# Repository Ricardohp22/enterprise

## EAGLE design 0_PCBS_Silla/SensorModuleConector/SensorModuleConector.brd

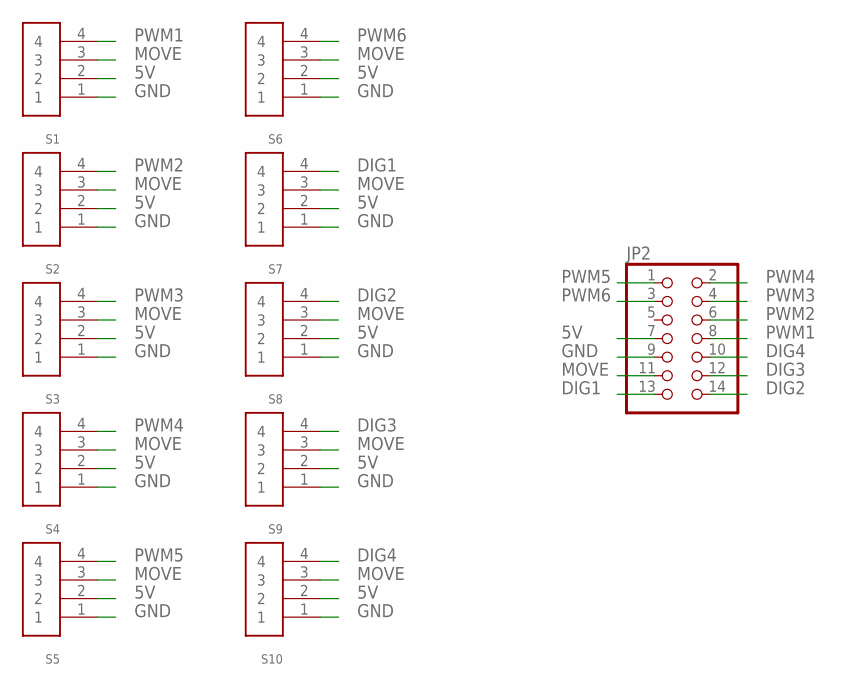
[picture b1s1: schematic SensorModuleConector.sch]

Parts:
JP2: PINHD-2X7; 2X07
S1, S2, S3, S4, S5, S6, S7, S8, S9, S10: CP150_1X4

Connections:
5V: JP2.7, S1.2, S2.2, S3.2, S4.2, S5.2, S6.2, S7.2, S8.2, S9.2, S10.2
DIG1: JP2.13, S7.4
DIG2: JP2.14, S8.4
DIG3: JP2.12, S9.4
DIG4: JP2.10, S10.4
GND: JP2.9, S1.1, S2.1, S3.1, S4.1, S5.1, S6.1, S7.1, S8.1, S9.1, S10.1
MOVE: JP2.11, S1.3, S2.3, S3.3, S4.3, S5.3, S6.3, S7.3, S8.3, S9.3, S10.3
PWM1: JP2.8, S1.4
PWM2: JP2.6, S2.4
PWM3: JP2.4, S3.4
PWM4: JP2.2, S4.4
PWM5: JP2.1, S5.4
PWM6: JP2.3, S6.4

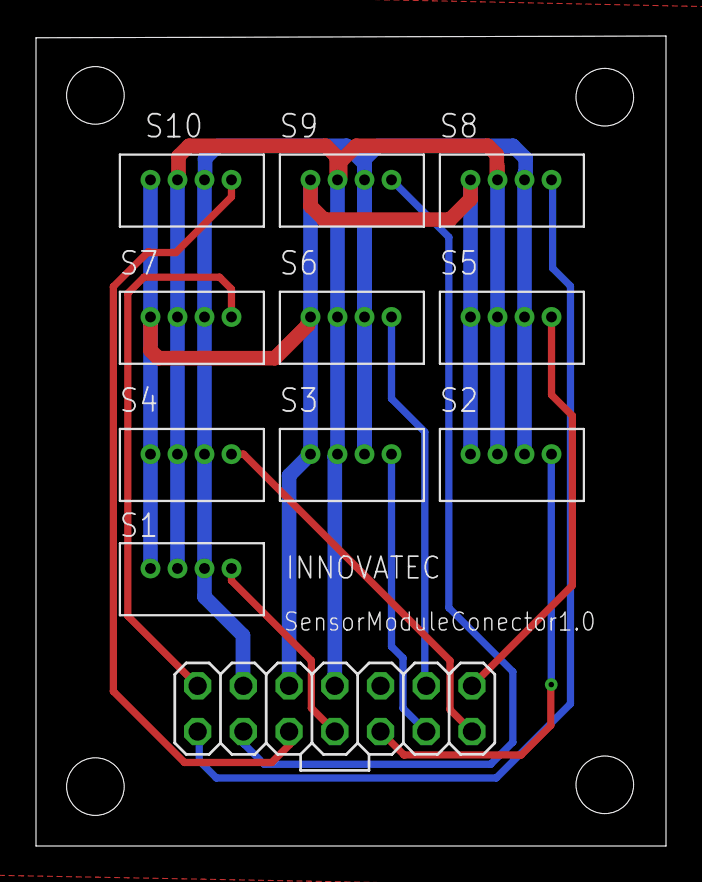
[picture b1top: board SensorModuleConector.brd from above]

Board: 2 copper layers, 35.0 x 45.0 mm, 11 parts (0 on the bottom side), 13 nets.

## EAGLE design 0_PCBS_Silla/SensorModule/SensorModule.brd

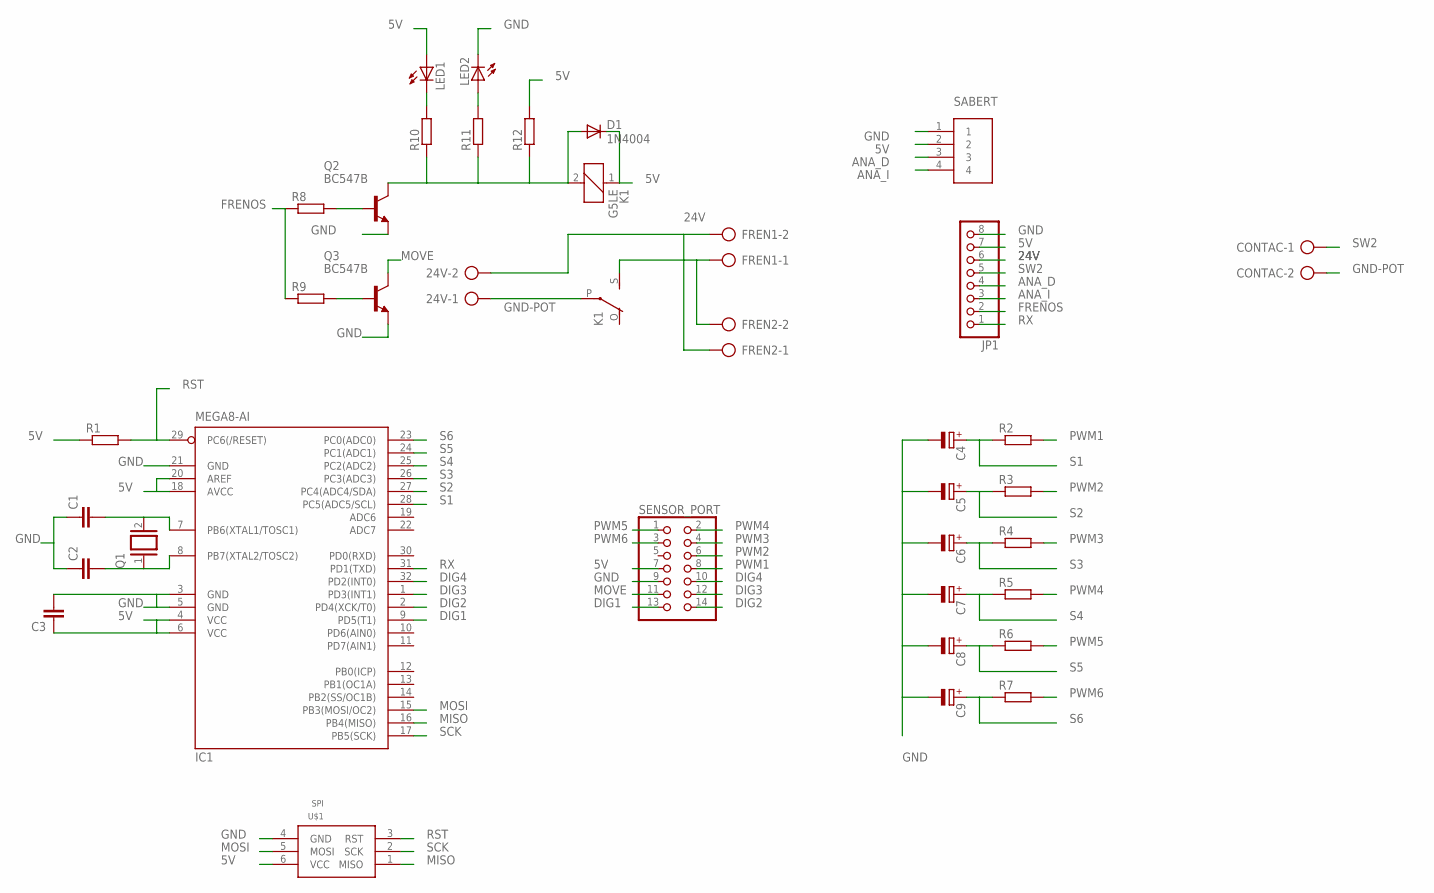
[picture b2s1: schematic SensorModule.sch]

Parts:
24V: AK500/2
C1, C2, C3: C-EUC0402K; C0402K
C4, C5, C6, C7, C8, C9: CPOL-EU153CLV-0505; 153CLV-0505
CONTAC: AK500/2
D1: 1N4004; DO41-10
FREN1, FREN2: AK500/2
IC1: MEGA8-AI; TQFP32-08
JP1: PINHD-1X8; 1X08
K1: G5LE
LED1, LED2: LEDCHIP-LED0603; CHIP-LED0603
Q1: XTAL/S; QS
Q2, Q3: BC547B; TO92
R1, R2, R3, R4, R5, R6, R7, R8, R9, R10, R11, R12: R-EU_M1206; M1206
SABERT: CP2_1X4
SENSOR_PORT: PINHD-2X7; 2X07
U$1: SPI; HEAD-2X3

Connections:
5V: C3.1, D1.C, IC1.4 (VCC), IC1.6 (VCC), IC1.18 (AVCC), IC1.20 (AREF), JP1.7, K1.1, LED1.A, R1.1, R12.2, SABERT.2, SENSOR_PORT.7, U$1.6 (VCC)
24V: 24V.2, FREN1.2, FREN2.1, JP1.6
ANA_D: JP1.4, SABERT.3
ANA_I: JP1.3, SABERT.4
DIG1: IC1.9 (PD5(T1)), SENSOR_PORT.13
DIG2: IC1.2 (PD4(XCK/T0)), SENSOR_PORT.14
DIG3: IC1.1 (PD3(INT1)), SENSOR_PORT.12
DIG4: IC1.32 (PD2(INT0)), SENSOR_PORT.10
FRENOS: JP1.2, R8.1, R9.1
GND: C1.1, C2.1, C3.2, C4.-, C5.-, C6.-, C7.-, C8.-, C9.-, IC1.3 (GND), IC1.5 (GND), IC1.21 (GND), JP1.8, LED2.C, Q2.1 (E), Q3.1 (E), SABERT.1, SENSOR_PORT.9, U$1.4 (GND)
GND-POT: 24V.1, CONTAC.2, K1.P
MISO: IC1.16 (PB4(MISO)), U$1.1 (MISO)
MOSI: IC1.15 (PB3(MOSI/OC2)), U$1.5 (MOSI)
MOVE: Q3.3 (C), SENSOR_PORT.11
unnamed: Q2.2 (B), R8.2
unnamed: D1.A, K1.2, Q2.3 (C), R10.1, R11.1, R12.1
unnamed: FREN1.1, FREN2.2, K1.S
unnamed: Q3.2 (B), R9.2
unnamed: LED1.C, R10.2
unnamed: C1.2, IC1.7 (PB6(XTAL1/TOSC1)), Q1.2
unnamed: C2.2, IC1.8 (PB7(XTAL2/TOSC2)), Q1.1
unnamed: LED2.A, R11.2
PWM1: R2.2, SENSOR_PORT.8
PWM2: R3.2, SENSOR_PORT.6
PWM3: R4.2, SENSOR_PORT.4
PWM4: R5.2, SENSOR_PORT.2
PWM5: R6.2, SENSOR_PORT.1
PWM6: R7.2, SENSOR_PORT.3
RST: IC1.29 (PC6(/RESET)), R1.2, U$1.3 (RST)
RX: IC1.31 (PD1(TXD)), JP1.1
S1: C4.+, IC1.28 (PC5(ADC5/SCL)), R2.1
S2: C5.+, IC1.27 (PC4(ADC4/SDA)), R3.1
S3: C6.+, IC1.26 (PC3(ADC3)), R4.1
S4: C7.+, IC1.25 (PC2(ADC2)), R5.1
S5: C8.+, IC1.24 (PC1(ADC1)), R6.1
S6: C9.+, IC1.23 (PC0(ADC0)), R7.1
SCK: IC1.17 (PB5(SCK)), U$1.2 (SCK)
SW2: CONTAC.1, JP1.5

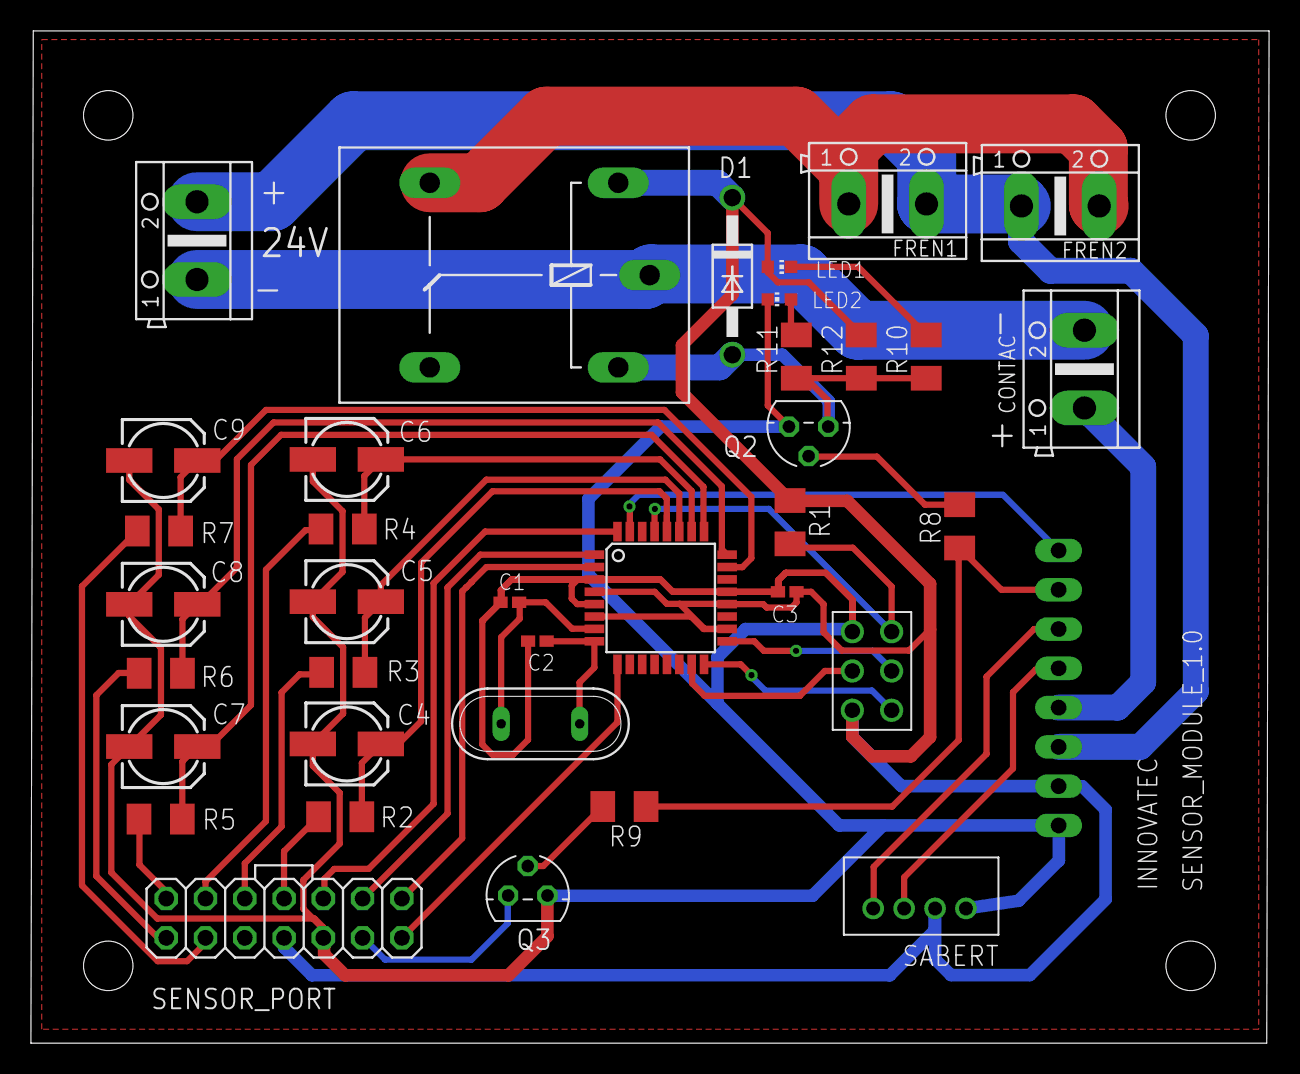
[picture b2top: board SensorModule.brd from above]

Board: 2 copper layers, 80.1 x 65.5 mm, 37 parts (0 on the bottom side), 38 nets.

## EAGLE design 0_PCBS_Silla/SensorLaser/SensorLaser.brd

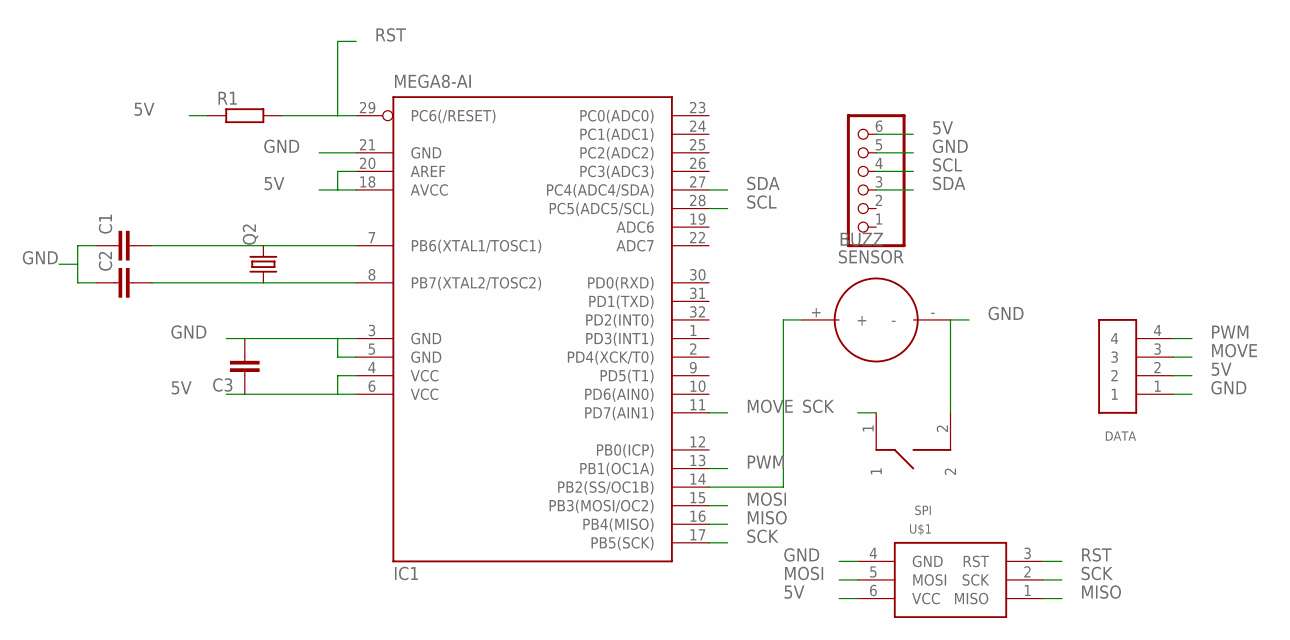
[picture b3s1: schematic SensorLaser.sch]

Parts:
BUZZ: KSQ-601BP
C1, C2, C3: C-EUC0402K; C0402K
DATA: CP150_1X4
IC1: MEGA8-AI; TQFP32-08
Q2: CRYSTALHC49U70; HC49U70
R1: R-EU_M1206; M1206
SENSOR: PINHD-1X6; 1X06
U$1: SPI; HEAD-2X3
U$2: PUSH_MEC; PUSH_MECANICO

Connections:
5V: C3.1, DATA.2, IC1.4 (VCC), IC1.6 (VCC), IC1.18 (AVCC), IC1.20 (AREF), R1.1, SENSOR.6, U$1.6 (VCC)
GND: BUZZ.-, C1.1, C2.1, C3.2, DATA.1, IC1.3 (GND), IC1.5 (GND), IC1.21 (GND), SENSOR.5, U$1.4 (GND), U$2.2
MISO: IC1.16 (PB4(MISO)), U$1.1 (MISO)
MOSI: IC1.15 (PB3(MOSI/OC2)), U$1.5 (MOSI)
MOVE: DATA.3, IC1.11 (PD7(AIN1))
unnamed: BUZZ.+, IC1.14 (PB2(SS/OC1B))
unnamed: C2.2, IC1.8 (PB7(XTAL2/TOSC2)), Q2.1
unnamed: C1.2, IC1.7 (PB6(XTAL1/TOSC1)), Q2.2
PWM: DATA.4, IC1.13 (PB1(OC1A))
RST: IC1.29 (PC6(/RESET)), R1.2, U$1.3 (RST)
SCK: IC1.17 (PB5(SCK)), U$1.2 (SCK), U$2.1
SCL: IC1.28 (PC5(ADC5/SCL)), SENSOR.4
SDA: IC1.27 (PC4(ADC4/SDA)), SENSOR.3

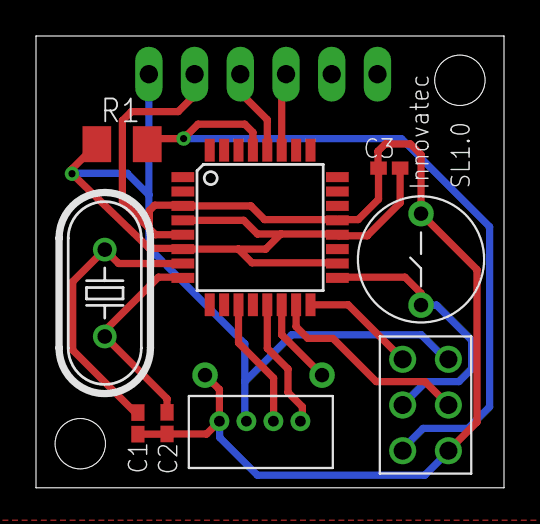
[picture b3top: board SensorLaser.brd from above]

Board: 2 copper layers, 26.0 x 25.1 mm, 11 parts (1 on the bottom side), 13 nets.

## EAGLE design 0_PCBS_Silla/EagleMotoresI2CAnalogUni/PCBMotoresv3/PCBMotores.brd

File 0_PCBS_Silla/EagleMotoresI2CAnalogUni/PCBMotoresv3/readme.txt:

PCB Motores v2 - Estatus: Completo
----------------
-Control de motores con sabertooth salidas analógicas
-Incorporacion de pin RX para comunicacion con modulo de sensores

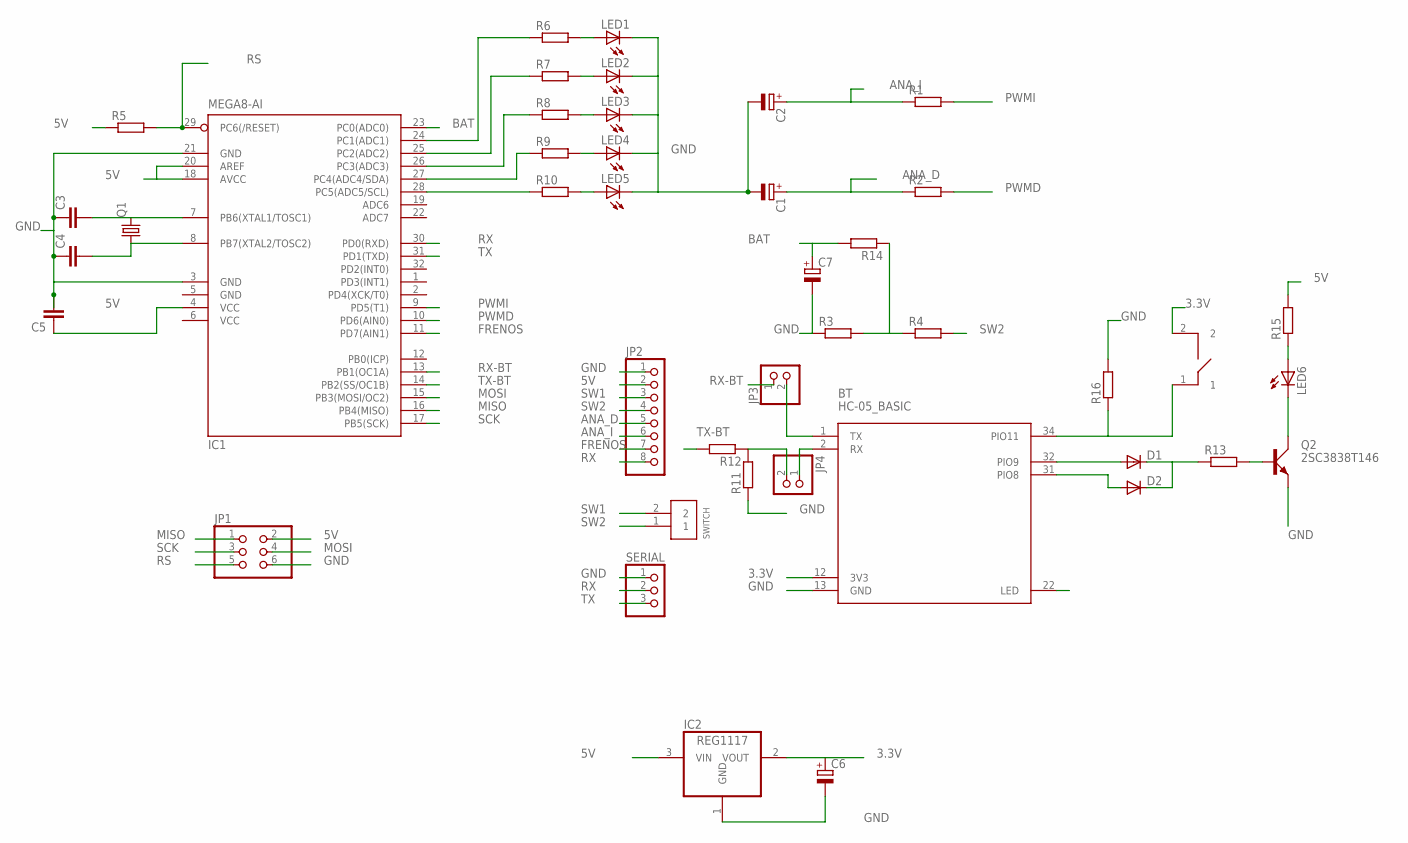
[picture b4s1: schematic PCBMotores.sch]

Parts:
BT: HC-05_BASIC; BLUETOOTH_SMD
C1, C2, C6, C7: CPOL-EU153CLV-0505; 153CLV-0505
C3, C4, C5: C-EUC0402K; C0402K
D1, D2: DIODE-DO-214AC; DO-214AC
IC1: MEGA8-AI; TQFP32-08
IC2: REG1117; SOT223
JP1: PINHD-2X3; 2X03
JP2: PINHD-1X8; 1X08
JP3, JP4: PINHD-1X2; 1X02
LED1, LED2, LED3, LED4, LED5: LED5MM
LED6: LED_ESML0603; LED_SML0603
Q1: CRYSTALHC49S; HC49/S
Q2: 2SC3838T146; SC59
R1, R2, R3, R4, R5, R6, R7, R8, R9, R10, R11, R12, R13, R14, R15, R16: R-EU_M1206; M1206
SERIAL: PINHD-1X3; 1X03
SWITCH: CP150_1X2
U$2: PUSH_SMD

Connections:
3.3V: BT.12 (3V3), C6.+, IC2.2 (VOUT), U$2.2
5V: C5.1, IC1.4 (VCC), IC1.18 (AVCC), IC1.20 (AREF), IC2.3 (VIN), JP1.2, JP2.2, R5.1, R15.2
ANA_D: C1.+, JP2.5, R2.1
ANA_I: C2.+, JP2.6, R1.1
BAT: C7.+, IC1.23 (PC0(ADC0)), R14.2
FRENOS: IC1.11 (PD7(AIN1)), JP2.7
GND: BT.13 (GND), C1.-, C2.-, C3.1, C4.1, C5.2, C6.-, C7.-, IC1.3 (GND), IC1.5 (GND), IC1.21 (GND), IC2.1 (GND), JP1.6, JP2.1, LED1.K (C), LED2.K (C), LED3.K (C), LED4.K (C), LED5.K (C), Q2.E, R3.1, R11.1, R16.2, SERIAL.1
MISO: IC1.16 (PB4(MISO)), JP1.1
MOSI: IC1.15 (PB3(MOSI/OC2)), JP1.4
unnamed: IC1.28 (PC5(ADC5/SCL)), R10.1
unnamed: IC1.27 (PC4(ADC4/SDA)), R9.1
unnamed: IC1.26 (PC3(ADC3)), R8.1
unnamed: C4.2, IC1.8 (PB7(XTAL2/TOSC2)), Q1.1
unnamed: C3.2, IC1.7 (PB6(XTAL1/TOSC1)), Q1.2
unnamed: IC1.25 (PC2(ADC2)), R7.1
unnamed: IC1.24 (PC1(ADC1)), R6.1
unnamed: LED1.A, R6.2
unnamed: LED2.A, R7.2
unnamed: LED3.A, R8.2
unnamed: LED4.A, R9.2
unnamed: LED5.A, R10.2
unnamed: D1.C, D2.C, R13.1
unnamed: Q2.B, R13.2
unnamed: BT.34 (PIO11), R16.1, U$2.1
unnamed: BT.32 (PIO9), D1.A
unnamed: BT.31 (PIO8), D2.A
unnamed: LED6.A, R15.1
unnamed: LED6.C, Q2.C
unnamed: JP4.2, R11.2, R12.1
unnamed: BT.1 (TX), JP3.2
unnamed: BT.2 (RX), JP4.1
unnamed: R3.2, R4.1, R14.1
PWMD: IC1.10 (PD6(AIN0)), R2.2
PWMI: IC1.9 (PD5(T1)), R1.2
RS: IC1.29 (PC6(/RESET)), JP1.5, R5.2
RX: IC1.30 (PD0(RXD)), JP2.8, SERIAL.2
RX-BT: IC1.13 (PB1(OC1A)), JP3.1
SCK: IC1.17 (PB5(SCK)), JP1.3
SW1: JP2.3, SWITCH.2
SW2: JP2.4, R4.2, SWITCH.1
TX: IC1.31 (PD1(TXD)), SERIAL.3
TX-BT: IC1.14 (PB2(SS/OC1B)), R12.2
VCC: IC1.6 (VCC)

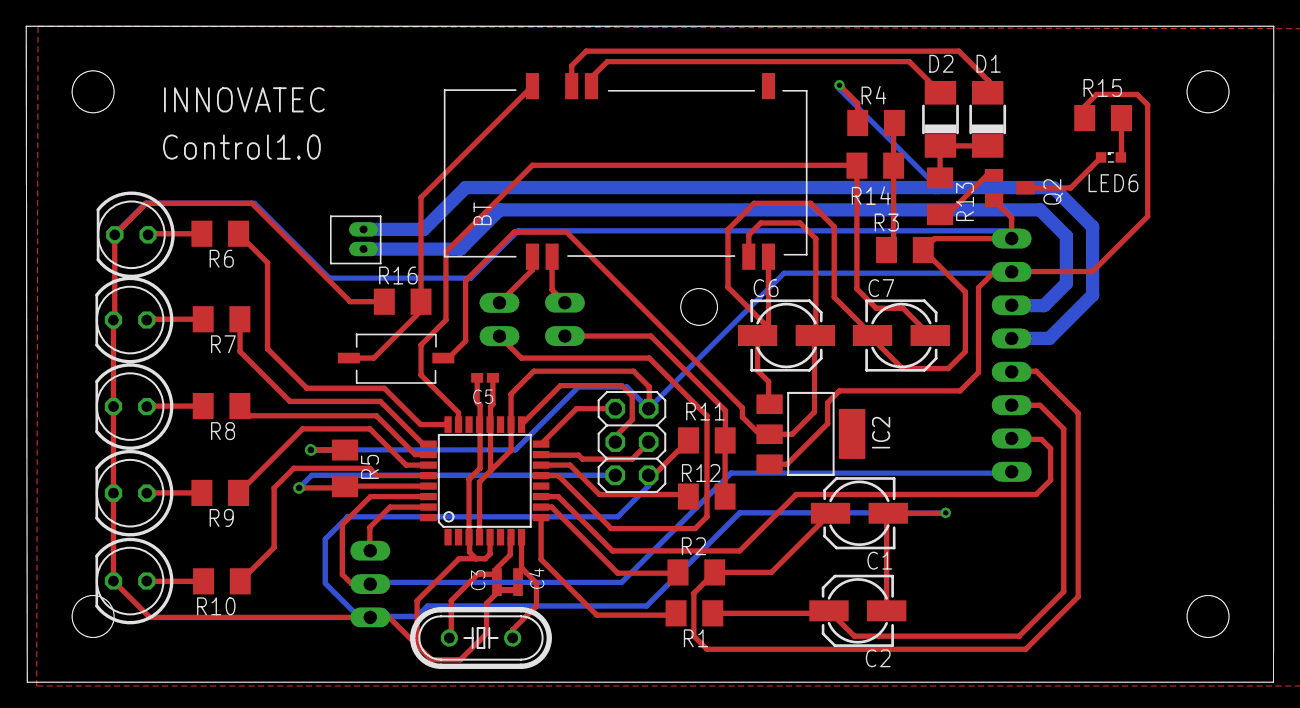
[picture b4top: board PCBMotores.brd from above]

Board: 2 copper layers, 95.1 x 50.0 mm, 43 parts (0 on the bottom side), 42 nets.

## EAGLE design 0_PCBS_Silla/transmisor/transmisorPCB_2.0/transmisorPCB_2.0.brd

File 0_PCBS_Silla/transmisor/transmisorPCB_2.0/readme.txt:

TransmisorPCB_2.0 - Estatus: Completo
----------------
-Lectura de mp5060 y envio de posicion por bluetooth

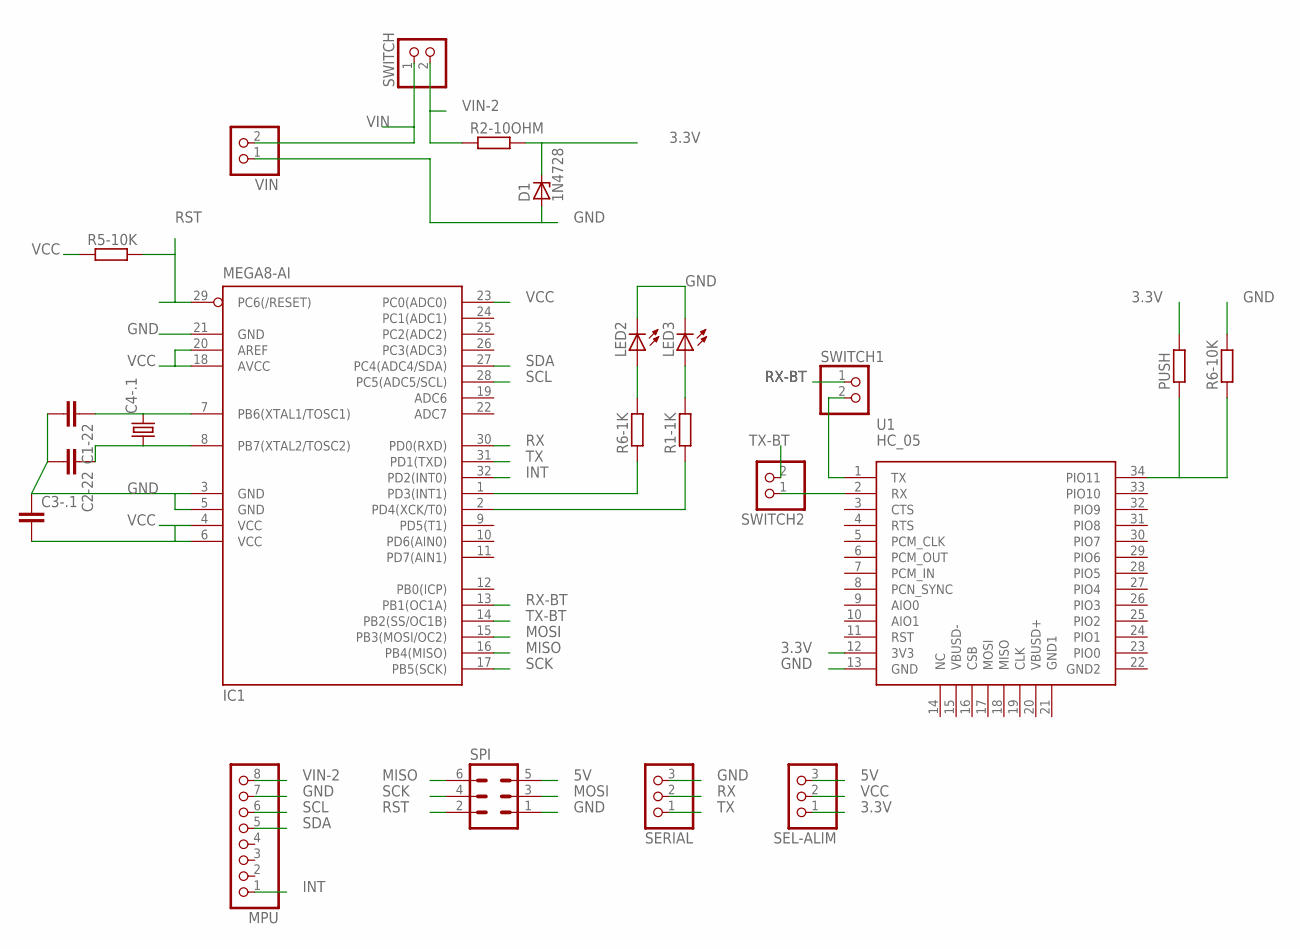
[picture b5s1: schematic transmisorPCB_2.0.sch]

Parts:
C1-22, C2-22, C3-.1: C-EUC0402K; C0402K
C4-.1: CRYSTALHC49U70; HC49U70
D1: 1N4728; DO41Z10
IC1: MEGA8-AI; TQFP32-08
LED2, LED3: LED_ESML0603; LED_SML0603
MPU: PINHD-1X8; 1X08
PUSH: R-EU_M2309; M2309
R1-1K, R5-10K, R6-1K, R6-10K: R-EU_M1206; M1206
R2-10OHM: R-EU_R2512; R2512
SEL-ALIM: PINHD-1X3; 1X03
SERIAL: PINHD-1X3; 1X03
SPI: MA03-2
SWITCH, SWITCH1, SWITCH2: PINHD-1X2; 1X02
U1: HC_05; BLUETOOTH_SMD
VIN: PINHD-1X2; 1X02

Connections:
3.3V: D1.C, PUSH.2, R2-10OHM.2, SEL-ALIM.1, U1.12 (3V3)
5V: SEL-ALIM.3, SPI.5
GND: C1-22.2, C2-22.2, C3-.1.1, D1.A, IC1.3 (GND), IC1.5 (GND), IC1.21 (GND), LED2.C, LED3.C, MPU.7, R6-10K.2, SERIAL.3, SPI.1, U1.13 (GND), VIN.1
INT: IC1.32 (PD2(INT0)), MPU.1
MISO: IC1.16 (PB4(MISO)), SPI.6
MOSI: IC1.15 (PB3(MOSI/OC2)), SPI.3
unnamed: IC1.2 (PD4(XCK/T0)), R1-1K.1
unnamed: SWITCH2.1, U1.2 (RX)
unnamed: C1-22.1, C4-.1.2, IC1.7 (PB6(XTAL1/TOSC1))
unnamed: C2-22.1, C4-.1.1, IC1.8 (PB7(XTAL2/TOSC2))
unnamed: IC1.1 (PD3(INT1)), R6-1K.1
unnamed: SWITCH1.2, U1.1 (TX)
unnamed: LED2.A, R6-1K.2
unnamed: LED3.A, R1-1K.2
unnamed: PUSH.1, R6-10K.1, U1.34 (PIO11)
RST: IC1.29 (PC6(/RESET)), R5-10K.2, SPI.2
RX: IC1.30 (PD0(RXD)), SERIAL.2
RX-BT: IC1.13 (PB1(OC1A)), SWITCH1.1
SCK: IC1.17 (PB5(SCK)), SPI.4
SCL: IC1.28 (PC5(ADC5/SCL)), MPU.6
SDA: IC1.27 (PC4(ADC4/SDA)), MPU.5
TX: IC1.31 (PD1(TXD)), SERIAL.1
TX-BT: IC1.14 (PB2(SS/OC1B)), SWITCH2.2
VCC: C3-.1.2, IC1.4 (VCC), IC1.6 (VCC), IC1.18 (AVCC), IC1.20 (AREF), IC1.23 (PC0(ADC0)), R5-10K.1, SEL-ALIM.2
VIN: SWITCH.1, VIN.2
VIN-2: MPU.8, R2-10OHM.1, SWITCH.2

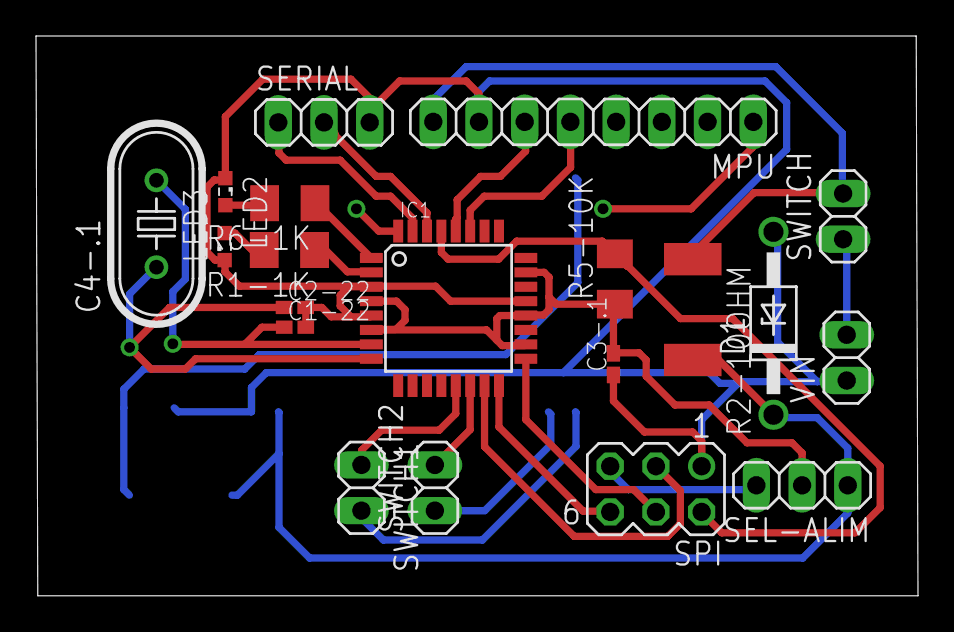
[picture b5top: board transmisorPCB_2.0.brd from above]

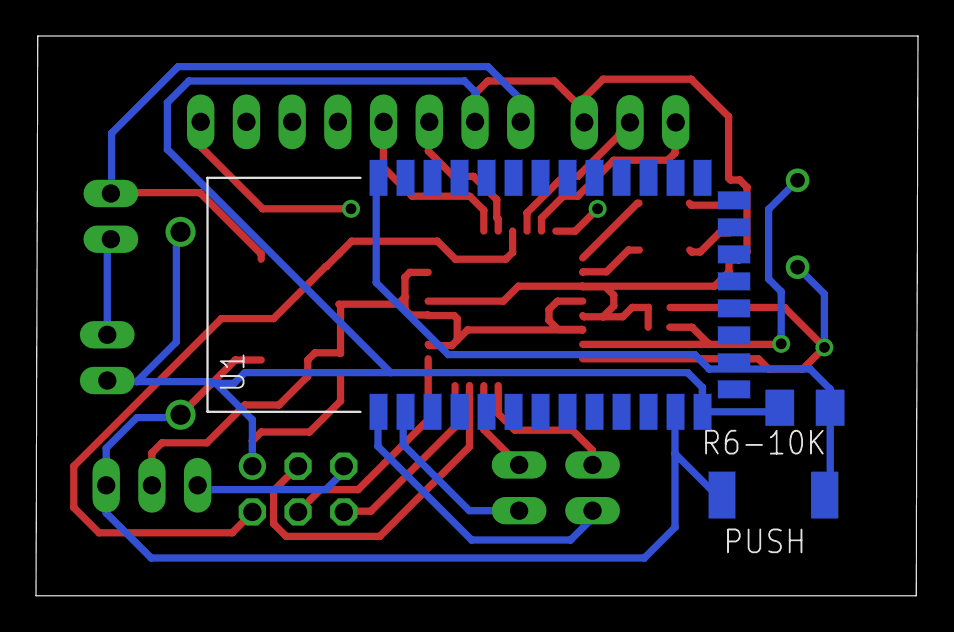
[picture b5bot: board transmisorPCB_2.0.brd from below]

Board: 2 copper layers, 49.0 x 31.1 mm, 23 parts (3 on the bottom side), 26 nets.

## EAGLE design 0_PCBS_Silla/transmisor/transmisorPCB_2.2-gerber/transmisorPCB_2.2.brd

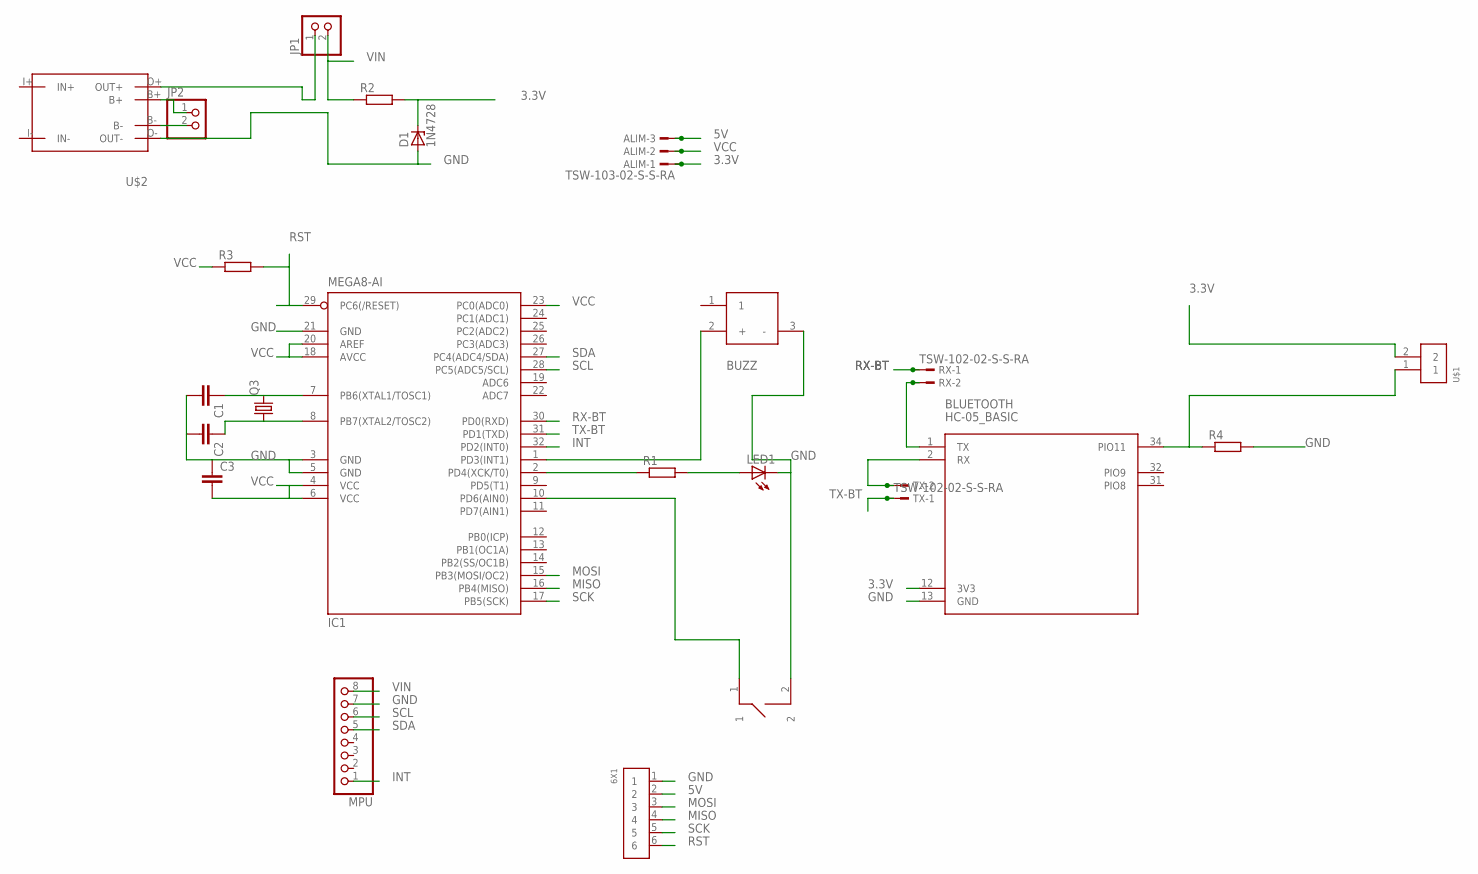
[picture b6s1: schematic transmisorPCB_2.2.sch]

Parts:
6X1: PINHEAD_1X6; PINHEAD_125_1X6
ALIM: TSW-103-02-S-S-RA
BLUETOOTH: HC-05_BASIC; BLUETOOTH_SMD
BUZZ: SM05ET02A
C1, C2, C3: C-EUC0402K; C0402K
D1: 1N4728; DO41Z10
IC1: MEGA8-AI; TQFP32-08
JP1, JP2: PINHD-1X2; 1X02
LED1: LEDCHIPLED-0603-TTW; CHIPLED-0603-TTW
MPU: PINHD-1X8; 1X08
PUSH: PUSH_SMD
Q3: CRYSTALHC49U70; HC49U70
R1, R3, R4: R-EU_M1206; M1206
R2: R-EU_R2512; R2512
RX: TSW-102-02-S-S-RA
TX: TSW-102-02-S-S-RA
U$1: CP150_1X2
U$2: TP4056

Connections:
3.3V: ALIM.1, BLUETOOTH.12 (3V3), D1.C, R2.2, U$1.2
5V: 6X1.2, ALIM.3
GND: 6X1.1, BLUETOOTH.13 (GND), BUZZ.3 (-), C1.2, C2.2, C3.1, D1.A, IC1.3 (GND), IC1.5 (GND), IC1.21 (GND), LED1.C@1 (C), MPU.7, PUSH.2, R4.2, U$2.O- (OUT-)
INT: IC1.32 (PD2(INT0)), MPU.1
MISO: 6X1.4, IC1.16 (PB4(MISO))
MOSI: 6X1.3, IC1.15 (PB3(MOSI/OC2))
unnamed: JP1.1, U$2.O+ (OUT+)
unnamed: BLUETOOTH.2 (RX), TX.2
unnamed: C1.1, IC1.7 (PB6(XTAL1/TOSC1)), Q3.2
unnamed: C2.1, IC1.8 (PB7(XTAL2/TOSC2)), Q3.1
unnamed: BUZZ.2 (+), IC1.1 (PD3(INT1))
unnamed: IC1.2 (PD4(XCK/T0)), R1.1
unnamed: JP2.2, U$2.B-
unnamed: BLUETOOTH.1 (TX), RX.2
unnamed: JP2.1, U$2.B+
unnamed: LED1.A@1 (A), R1.2
unnamed: BLUETOOTH.34 (PIO11), R4.1, U$1.1
unnamed: IC1.10 (PD6(AIN0)), PUSH.1
RST: 6X1.6, IC1.29 (PC6(/RESET)), R3.2
RX-BT: IC1.30 (PD0(RXD)), RX.1
SCK: 6X1.5, IC1.17 (PB5(SCK))
SCL: IC1.28 (PC5(ADC5/SCL)), MPU.6
SDA: IC1.27 (PC4(ADC4/SDA)), MPU.5
TX-BT: IC1.31 (PD1(TXD)), TX.1
VCC: ALIM.2, C3.2, IC1.4 (VCC), IC1.6 (VCC), IC1.18 (AVCC), IC1.20 (AREF), IC1.23 (PC0(ADC0)), R3.1
VIN: JP1.2, MPU.8, R2.1

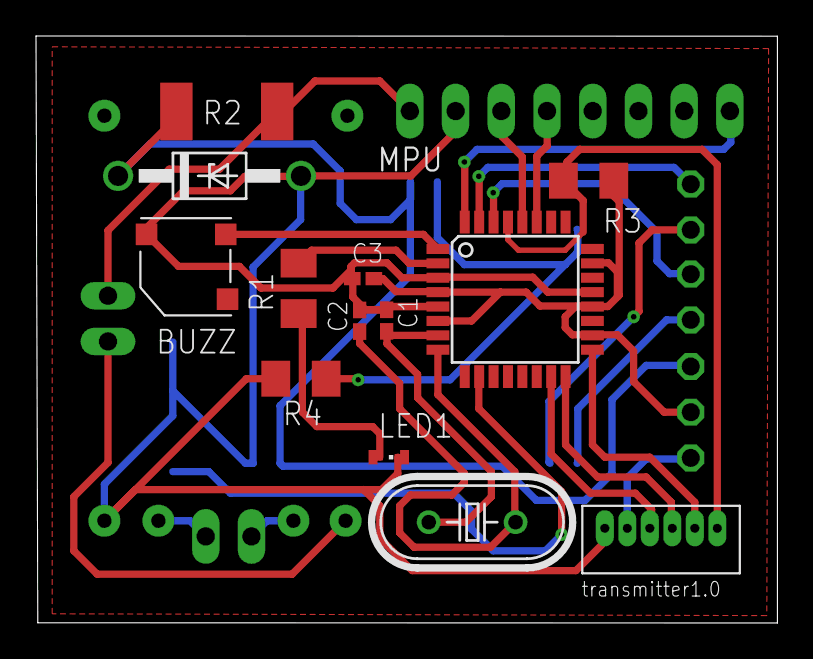
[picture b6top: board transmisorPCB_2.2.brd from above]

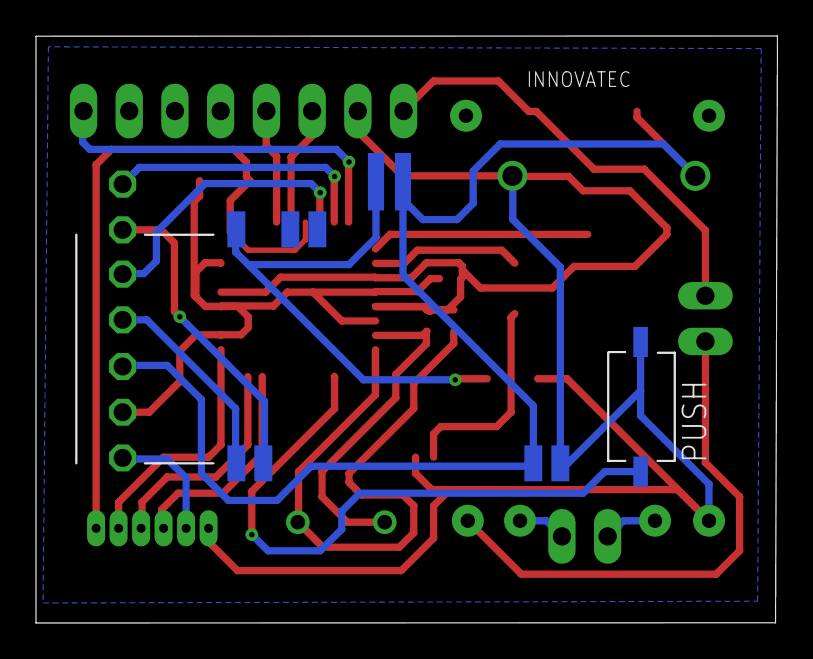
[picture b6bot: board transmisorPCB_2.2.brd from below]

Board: 2 copper layers, 41.2 x 32.6 mm, 23 parts (3 on the bottom side), 26 nets.

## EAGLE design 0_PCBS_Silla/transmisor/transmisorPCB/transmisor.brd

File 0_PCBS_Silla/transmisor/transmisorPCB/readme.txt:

TransmisorPCB - Estatus: No funcional
----------------
-Lectura de mp5060 y envio de posicion por bluetooth

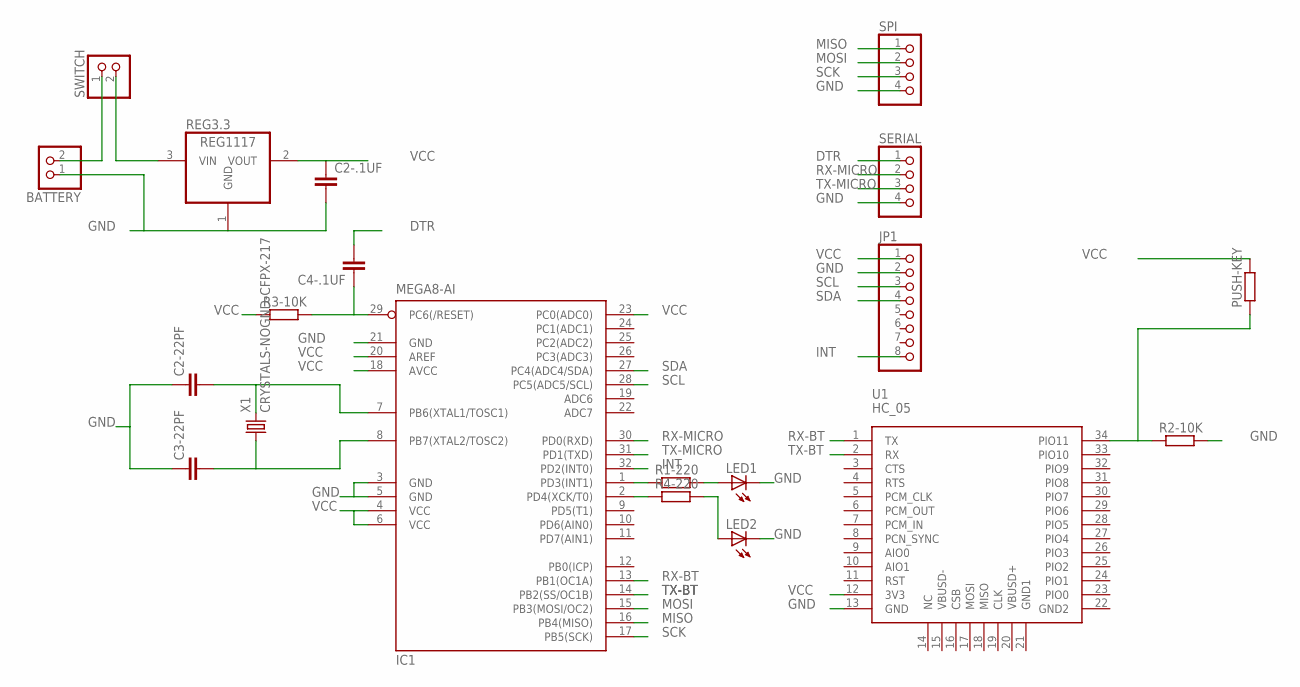
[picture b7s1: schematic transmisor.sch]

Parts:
BATTERY: PINHD-1X2; 1X02
C2-22PF, C2-.1UF, C3-22PF, C4-.1UF: C-EUC0805; C0805
IC1: MEGA8-AI; TQFP32-08
JP1: PINHD-1X8; 1X08
LED1, LED2: LEDMINI-TOP; OSRAM-MINI-TOP-LED
PUSH-KEY: R-EU_M5923; M5923
R1-220, R2-10K, R3-10K, R4-220: R-EU_M0805; M0805
REG3.3: REG1117; SOT223
SERIAL: PINHD-1X4; 1X04
SPI: PINHD-1X4; 1X04
SWITCH: PINHD-1X2; 1X02
U1: HC_05; BLUETOOTH_SMD
X1: CRYSTALS-NOGND-CFPX-217; 3.2X1.5-2-PAD

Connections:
DTR: C4-.1UF.2, SERIAL.1
GND: BATTERY.1, C2-22PF.1, C2-.1UF.2, C3-22PF.1, IC1.3 (GND), IC1.5 (GND), IC1.21 (GND), JP1.2, LED1.C, LED2.C, R2-10K.2, REG3.3.1 (GND), SERIAL.4, SPI.4, U1.13 (GND)
INT: IC1.32 (PD2(INT0)), JP1.8
MISO: IC1.16 (PB4(MISO)), SPI.1
MOSI: IC1.15 (PB3(MOSI/OC2)), SPI.2
unnamed: IC1.1 (PD3(INT1)), R1-220.1
unnamed: LED1.A, R1-220.2
unnamed: C2-22PF.2, IC1.7 (PB6(XTAL1/TOSC1)), X1.2
unnamed: C3-22PF.2, IC1.8 (PB7(XTAL2/TOSC2)), X1.1
unnamed: IC1.2 (PD4(XCK/T0)), R4-220.1
unnamed: LED2.A, R4-220.2
unnamed: C4-.1UF.1, IC1.29 (PC6(/RESET)), R3-10K.2
unnamed: PUSH-KEY.1, R2-10K.1, U1.34 (PIO11)
unnamed: BATTERY.2, SWITCH.1
unnamed: REG3.3.3 (VIN), SWITCH.2
RX-BT: IC1.13 (PB1(OC1A)), U1.1 (TX)
RX-MICRO: IC1.30 (PD0(RXD)), SERIAL.2
SCK: IC1.17 (PB5(SCK)), SPI.3
SCL: IC1.28 (PC5(ADC5/SCL)), JP1.3
SDA: IC1.27 (PC4(ADC4/SDA)), JP1.4
TX-BT: IC1.14 (PB2(SS/OC1B)), U1.2 (RX)
TX-MICRO: IC1.31 (PD1(TXD)), SERIAL.3
VCC: C2-.1UF.1, IC1.4 (VCC), IC1.6 (VCC), IC1.18 (AVCC), IC1.20 (AREF), IC1.23 (PC0(ADC0)), JP1.1, PUSH-KEY.2, R3-10K.1, REG3.3.2 (VOUT), U1.12 (3V3)

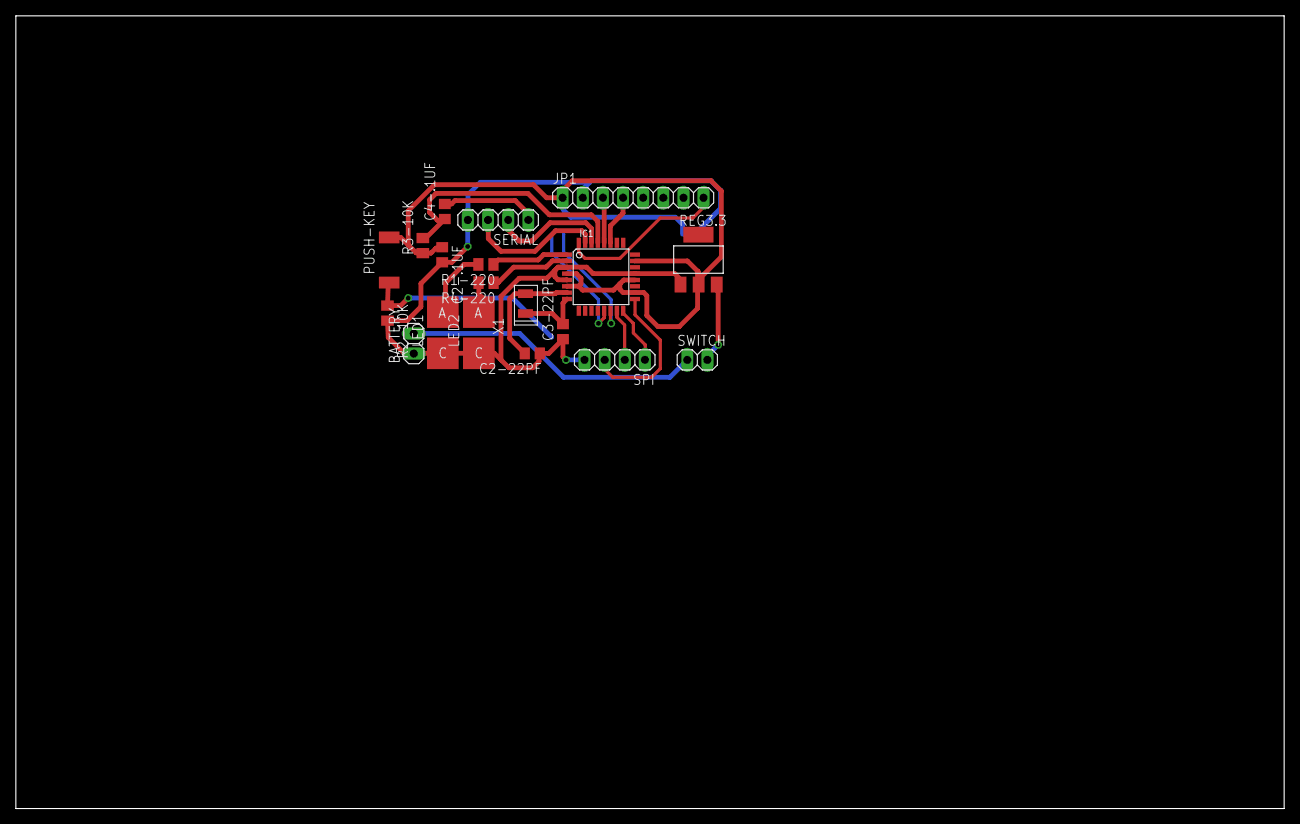
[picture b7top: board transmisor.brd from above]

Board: 2 copper layers, 160.0 x 100.0 mm, 20 parts (1 on the bottom side), 23 nets.

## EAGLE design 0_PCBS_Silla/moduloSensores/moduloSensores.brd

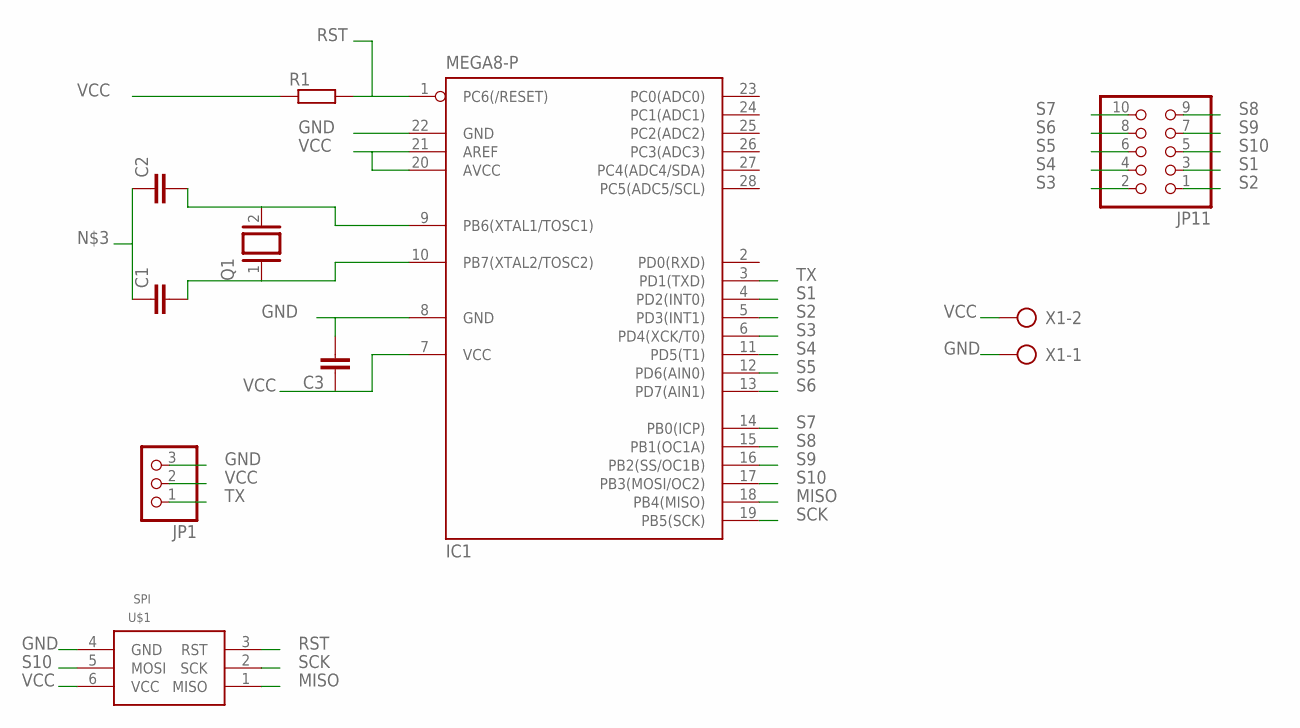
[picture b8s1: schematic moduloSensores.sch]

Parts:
C1, C2, C3: C-EU050-025X075; C050-025X075
IC1: MEGA8-P; DIL28-3
JP1: PINHD-1X3; 1X03
JP11: PINHD-2X5; 2X05
Q1: XTAL/S; QS
R1: R-EU_0204/7; 0204/7
U$1: SPI; HEAD-2X3
X1: AK500/2

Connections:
GND: C3.2, IC1.8 (GND), IC1.22 (GND), JP1.3, U$1.4 (GND), X1.1
MISO: IC1.18 (PB4(MISO)), U$1.1 (MISO)
unnamed: C2.2, IC1.9 (PB6(XTAL1/TOSC1)), Q1.2
unnamed: C1.2, IC1.10 (PB7(XTAL2/TOSC2)), Q1.1
unnamed: C1.1, C2.1
RST: IC1.1 (PC6(/RESET)), R1.2, U$1.3 (RST)
S1: IC1.4 (PD2(INT0)), JP11.3
S2: IC1.5 (PD3(INT1)), JP11.1
S3: IC1.6 (PD4(XCK/T0)), JP11.2
S4: IC1.11 (PD5(T1)), JP11.4
S5: IC1.12 (PD6(AIN0)), JP11.6
S6: IC1.13 (PD7(AIN1)), JP11.8
S7: IC1.14 (PB0(ICP)), JP11.10
S8: IC1.15 (PB1(OC1A)), JP11.9
S9: IC1.16 (PB2(SS/OC1B)), JP11.7
S10: IC1.17 (PB3(MOSI/OC2)), JP11.5, U$1.5 (MOSI)
SCK: IC1.19 (PB5(SCK)), U$1.2 (SCK)
TX: IC1.3 (PD1(TXD)), JP1.1
VCC: C3.1, IC1.7 (VCC), IC1.20 (AVCC), IC1.21 (AREF), JP1.2, R1.1, U$1.6 (VCC), X1.2
